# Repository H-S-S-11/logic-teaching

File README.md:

# logic-teaching
PCB for teaching logic principles to primary and secondary school children.

Board has spaces for a dual AA battery holder for power, 4 LEDs, 4 pushbuttons and pullup/down resistors, 4 SPDT switches, and 2 DIP-14 sockets.

Most connections apart from power to ICs and protection resistors will be made by students via the connectors available. Any user connections to power rails will go through a soldered-on protection resistor to limit short circuit current.

Switches, LEDs and pushbuttons will have easy-to-use connections (bananna plugs, wire loop test points) as well as standard 0.1" headers used by other components.

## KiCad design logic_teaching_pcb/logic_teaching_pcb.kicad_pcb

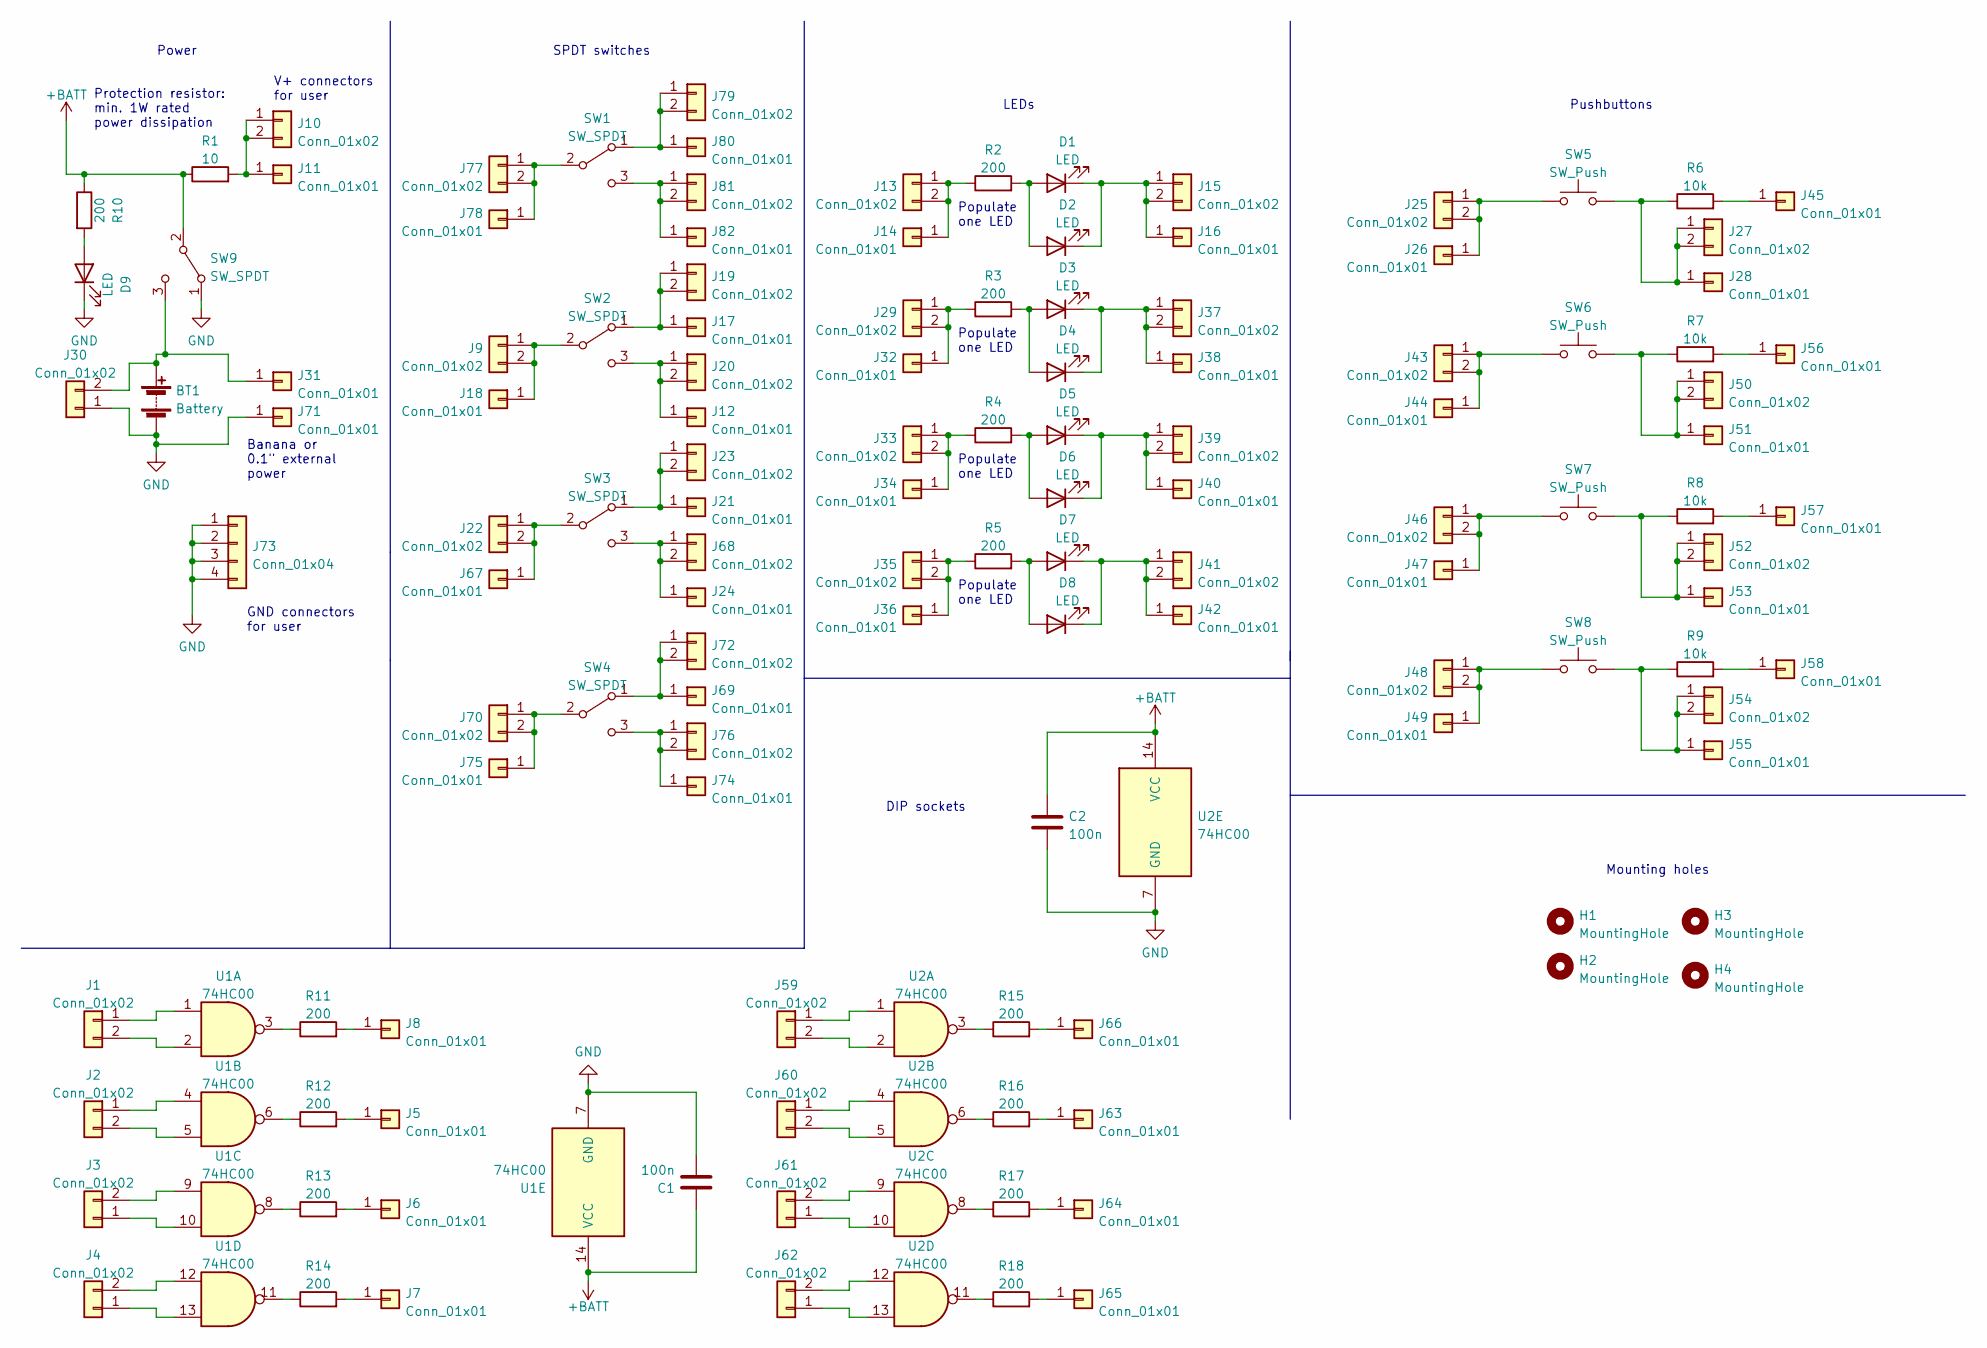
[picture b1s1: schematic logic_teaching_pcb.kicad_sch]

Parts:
BT1: Battery; BatteryHolder_Keystone_2462_2xAA
C1, C2: 100n; C_1206_3216Metric_Pad1.33x1.80mm_HandSolder
D1, D3, D5, D7, D9: LED; LED_1206_3216Metric_Pad1.42x1.75mm_HandSolder
D2, D4, D6, D8: LED; LED_D5.0mm
H1, H2, H3, H4: MountingHole; MountingHole_4.3mm_M4
J1, J2, J3, J4, J9, J10, J13, J15, J19, J20, J22, J23, J25, J27, J29, J30, J33, J35, J37, J39, J41, J43, J46, J48, J50, J52, J54, J59, J60, J61, J62, J68, J70, J72, J76, J77, J79, J81: Conn_01x02; PinHeader_1x02_P2.54mm_Vertical
J5, J6, J7, J8, J45, J56, J57, J58, J63, J64, J65, J66: Conn_01x01; PinHeader_1x01_P2.54mm_Vertical
J11, J12, J14, J16, J17, J18, J21, J24, J26, J28, J31, J32, J34, J36, J38, J40, J42, J44, J47, J49, J51, J53, J55, J67, J69, J71, J74, J75, J78, J80, J82: Conn_01x01; BindingPost_Shin_Chin_R1-9
J73: Conn_01x04; PinHeader_2x02_P2.54mm_Vertical
R1: 10; R_Axial_Power_L20.0mm_W6.4mm_P22.40mm
R2, R3, R4, R5, R10, R11, R12, R13, R14, R15, R16, R17, R18: 200; R_1206_3216Metric_Pad1.30x1.75mm_HandSolder
R6, R7, R8, R9: 10k; R_1206_3216Metric_Pad1.30x1.75mm_HandSolder
SW1, SW2, SW3, SW4, SW9: SW_SPDT; SW_Slide_1P2T_CK_OS102011MS2Q
SW5, SW6, SW7, SW8: SW_Push; SW_PUSH-12mm
U1, U2: 74HC00; DIP-14_W7.62mm_Socket

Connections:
+BATT: C1.1, C2.1, R1.1, R10.1, SW9.2 (B), U1.14 (VCC), U2.14 (VCC)
GND: BT1.2 (-), C1.2, C2.2, D9.1 (K), J30.1, J71.1, J73.1, J73.2, J73.3, J73.4, SW9.1 (A), U1.7 (GND), U2.7 (GND)
unnamed: BT1.1 (+), J30.2, J31.1, SW9.3 (C)
unnamed: D1.1 (K), D2.1 (K), J15.1, J15.2, J16.1
unnamed: D1.2 (A), D2.2 (A), R2.2
unnamed: D3.1 (K), D4.1 (K), J37.1, J37.2, J38.1
unnamed: D3.2 (A), D4.2 (A), R3.2
unnamed: D5.1 (K), D6.1 (K), J39.1, J39.2, J40.1
unnamed: D5.2 (A), D6.2 (A), R4.2
unnamed: D7.1 (K), D8.1 (K), J41.1, J41.2, J42.1
unnamed: D7.2 (A), D8.2 (A), R5.2
unnamed: D9.2 (A), R10.2
unnamed: J1.1, U1.1
unnamed: J1.2, U1.2
unnamed: J2.1, U1.4
unnamed: J2.2, U1.5
unnamed: J3.1, U1.10
unnamed: J3.2, U1.9
unnamed: J4.1, U1.13
unnamed: J4.2, U1.12
unnamed: J5.1, R12.2
unnamed: J6.1, R13.2
unnamed: J7.1, R14.2
unnamed: J8.1, R11.2
unnamed: J10.1, J10.2, J11.1, R1.2
unnamed: J12.1, J20.1, J20.2, SW2.3 (C)
unnamed: J13.1, J13.2, J14.1, R2.1
unnamed: J17.1, J19.1, J19.2, SW2.1 (A)
unnamed: J9.1, J9.2, J18.1, SW2.2 (B)
unnamed: J21.1, J23.1, J23.2, SW3.1 (A)
unnamed: J22.1, J22.2, J67.1, SW3.2 (B)
unnamed: J24.1, J68.1, J68.2, SW3.3 (C)
unnamed: J25.1, J25.2, J26.1, SW5.1
unnamed: J27.1, J27.2, J28.1, R6.1, SW5.2
unnamed: J29.1, J29.2, J32.1, R3.1
unnamed: J33.1, J33.2, J34.1, R4.1
unnamed: J35.1, J35.2, J36.1, R5.1
unnamed: J43.1, J43.2, J44.1, SW6.1
unnamed: J45.1, R6.2
unnamed: J46.1, J46.2, J47.1, SW7.1
unnamed: J48.1, J48.2, J49.1, SW8.1
unnamed: J50.1, J50.2, J51.1, R7.1, SW6.2
unnamed: J52.1, J52.2, J53.1, R8.1, SW7.2
unnamed: J54.1, J54.2, J55.1, R9.1, SW8.2
unnamed: J56.1, R7.2
unnamed: J57.1, R8.2
unnamed: J58.1, R9.2
unnamed: J59.1, U2.1
unnamed: J59.2, U2.2
unnamed: J60.1, U2.4
unnamed: J60.2, U2.5
unnamed: J61.1, U2.10
unnamed: J61.2, U2.9
unnamed: J62.1, U2.13
unnamed: J62.2, U2.12
unnamed: J63.1, R16.2
unnamed: J64.1, R17.2
unnamed: J65.1, R18.2
unnamed: J66.1, R15.2
unnamed: J69.1, J72.1, J72.2, SW4.1 (A)
unnamed: J70.1, J70.2, J75.1, SW4.2 (B)
unnamed: J74.1, J76.1, J76.2, SW4.3 (C)
unnamed: J79.1, J79.2, J80.1, SW1.1 (A)
unnamed: J77.1, J77.2, J78.1, SW1.2 (B)
unnamed: J81.1, J81.2, J82.1, SW1.3 (C)
unnamed: R11.1, U1.3
unnamed: R12.1, U1.6
unnamed: R13.1, U1.8
unnamed: R14.1, U1.11
unnamed: R15.1, U2.3
unnamed: R16.1, U2.6
unnamed: R17.1, U2.8
unnamed: R18.1, U2.11

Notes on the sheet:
V+ connectors for user
Power
Populate one LED
Banana or 0.1" external power
Mounting holes
GND connectors for user
Protection resistor: min. 1W rated power dissipation
DIP sockets
LEDs
SPDT switches
Pushbuttons

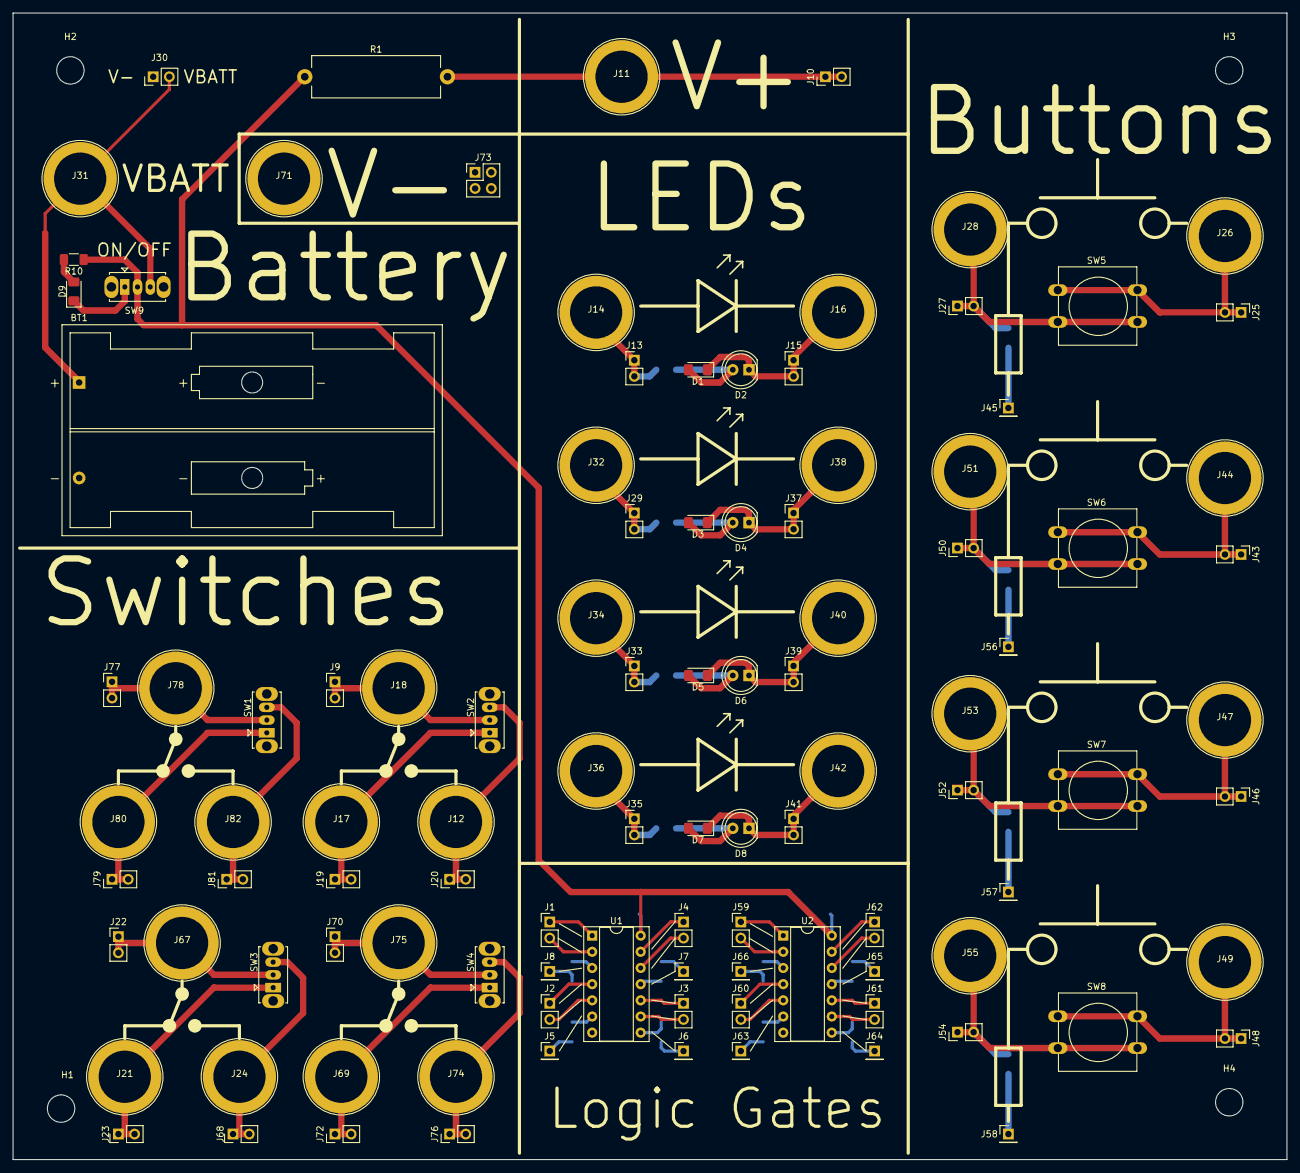
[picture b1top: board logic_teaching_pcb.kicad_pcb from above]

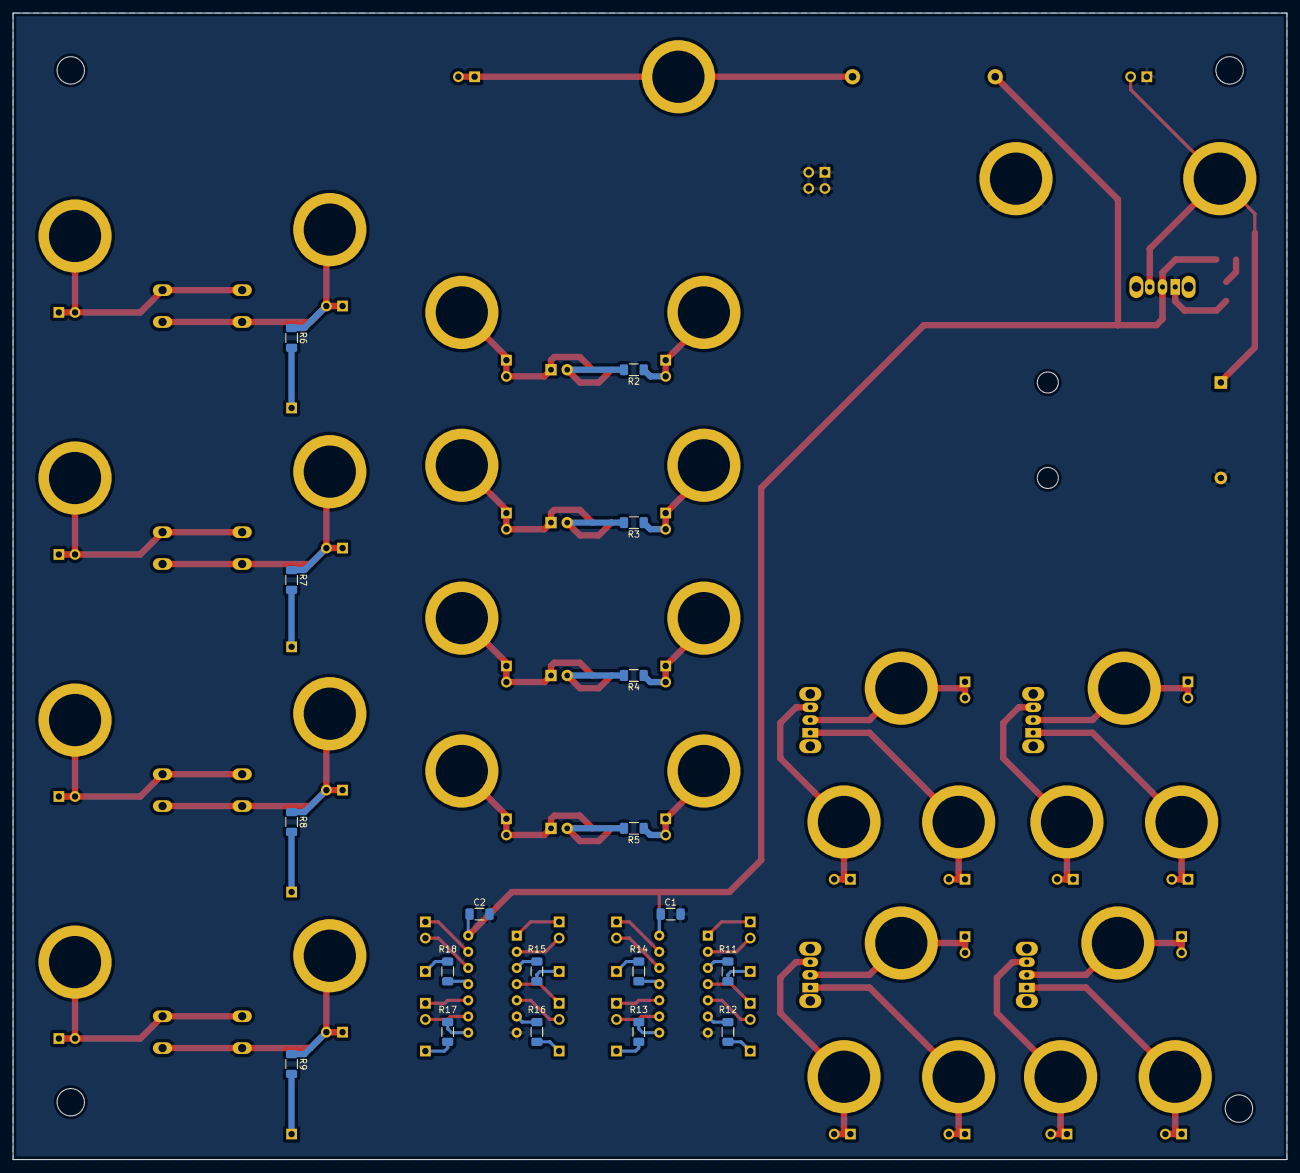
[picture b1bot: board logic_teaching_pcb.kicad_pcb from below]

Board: 2 copper layers, 200.0 x 180.0 mm, 127 parts (18 on the bottom side), 73 nets.

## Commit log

2022-10-25 PCB schematic, start layout
2022-10-25 remove backup files
2022-10-25 add backups to gitignore
2022-10-25 finish first PCB draft
2022-10-25 Added power switch
2022-10-25 print first draft overview
2022-10-26 change footprint to binding post, add to switches
